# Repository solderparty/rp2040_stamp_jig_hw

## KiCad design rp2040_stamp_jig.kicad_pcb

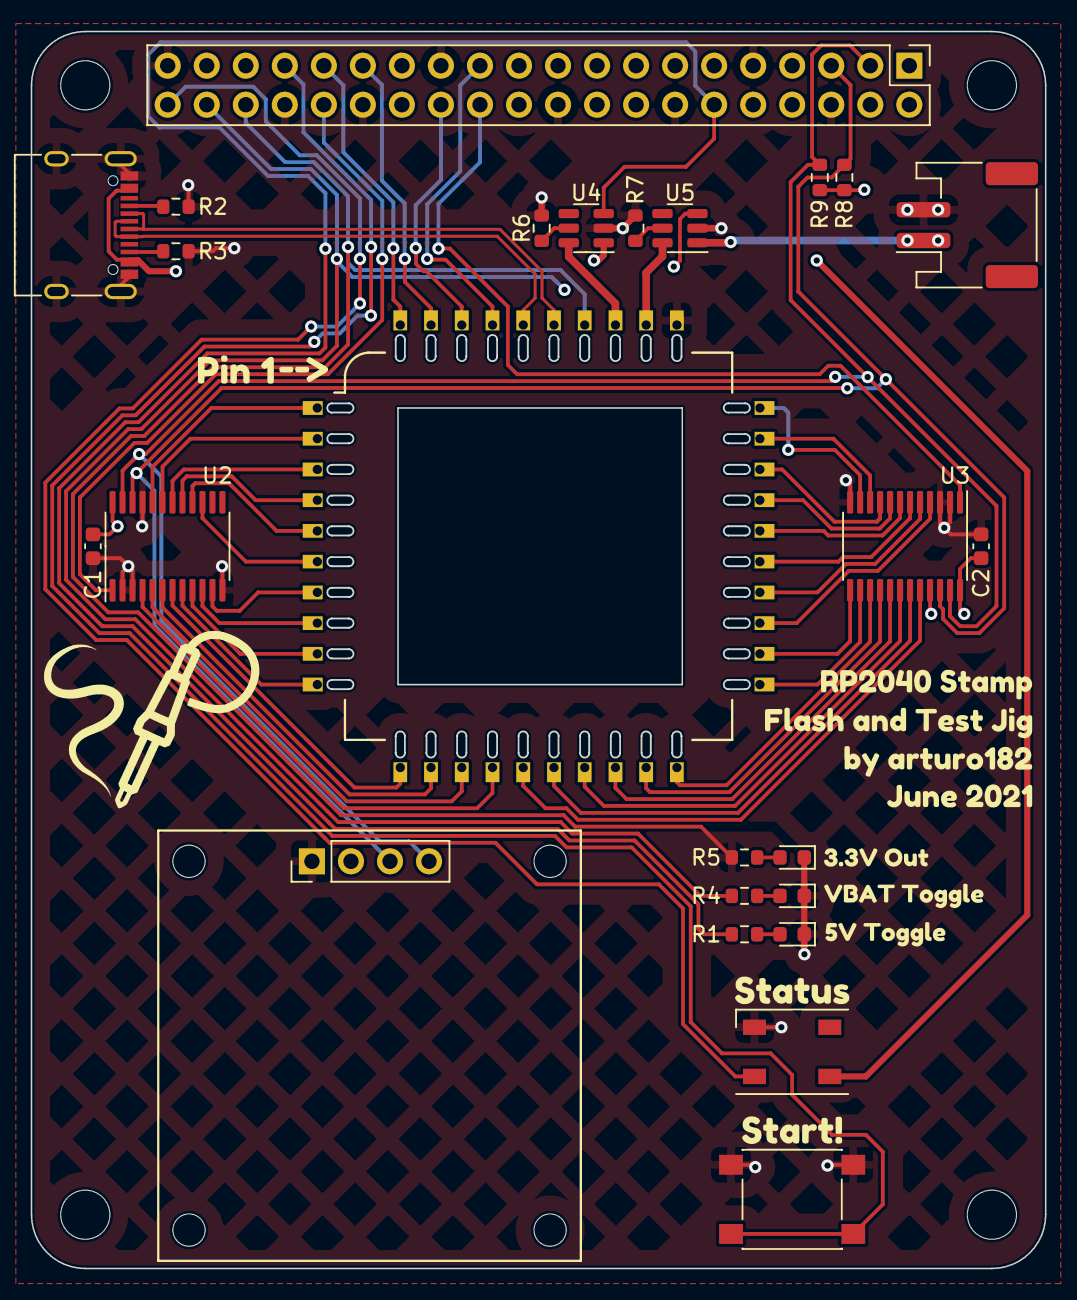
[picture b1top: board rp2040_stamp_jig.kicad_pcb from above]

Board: 4 copper layers, 66.0 x 80.5 mm, 81 parts (0 on the bottom side), 58 nets.

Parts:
C1, C2: 0.1uF; C_0603_1608Metric
D1: LED_5V_TGL; LED_0603_1608Metric
D2, D3: LED_VBAT_TGL; LED_0603_1608Metric
D4: WS2812B; LED_WS2812B_PLCC4_5.0x5.0mm_P3.2mm
H1, H2, H3, H4: MountingHole; MountingHole_3.2mm_M3
J1, J2, J3, J4, J5, J6, J7, J8, J9, J10, J11, J12, J13, J14, J15, J16, J17, J18, J19, J20, J21, J22, J23, J24, J25, J26, J27, J28, J29, J30, J31, J32, J33, J34, J35, J36, J37, J38, J39, J40: Conn_01x01; StampSpring_1x01_P1.00mm_Vertical
J41: USB_C_Receptacle_USB2.0; USB_C_Receptacle_XKB_U262-16XN-4BVC11
J42: Raspberry_Pi_2_3; PinHeader_2x20_P2.54mm_Vertical
J43: Conn_Batt; JST_PH_S2B-PH-SM4-TB_1x02-1MP_P2.00mm_Horizontal
J44: Conn_OLED; PinHeader_1x04_P2.54mm_Vertical
R1, R4, R5: 1K; R_0603_1608Metric
R2, R3: 5.1K; R_0603_1608Metric
R6, R7: 2K; R_0603_1608Metric
R8, R9: 4.7K; R_0603_1608Metric
SW1: BTN_START; SW_SPST_PTS645
U1: RP2040_Stamp; RP2040_Stamp_SMD
U2, U3: PCA9555PW; TSSOP-24_4.4x7.8mm_P0.65mm
U4, U5: TPS255xDBV; SOT-23-6
svg2mod, svg2mod#2, svg2mod#3, svg2mod#4, svg2mod#5, svg2mod#6, svg2mod#7, svg2mod#8, svg2mod#9, svg2mod#10, svg2mod#11, svg2mod#12: G***; svg2mod

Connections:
+3V3: C1.1, C2.1, J42.1 (3V3), J42.17 (3V3), J44.2, R8.1, R9.1, U2.24 (VDD), U3.21 (A0), U3.24 (VDD)
+5V: D4.1 (VDD), J41.A4 (VBUS), J41.A9 (VBUS), J41.B4 (VBUS), J41.B9 (VBUS), U4.1 (IN)
+BATT: J43.1, U5.1 (IN)
/3.3V_OUT: J3.1, J42.36 (GPIO16), R5.2
/5V_IN: J1.1, U4.6 (OUT)
/5V_TOGGLE: J42.12 (GPIO18/PWM0), R1.2, U4.3 (EN)
/BOOTSEL: J8.1, J42.31 (GCLK2/GPIO6)
/BUTTON: J42.33 (PWM1/GPIO13), SW1.1 (A)
/GPIO0: J2.1, U2.20 (IO1_7)
/GPIO1: J4.1, U2.19 (IO1_6)
/GPIO2: J6.1, U2.18 (IO1_5)
/GPIO3: J7.1, U2.17 (IO1_4)
/GPIO4: J9.1, U2.16 (IO1_3)
/GPIO5: J10.1, U2.15 (IO1_2)
/GPIO6: J12.1, U2.11 (IO0_7)
/GPIO7: J13.1, U2.10 (IO0_6)
/GPIO8: J15.1, U2.9 (IO0_5)
/GPIO9: J17.1, U2.8 (IO0_4)
/GPIO10: J18.1, U2.7 (IO0_3)
/GPIO11: J20.1, U2.6 (IO0_2)
/GPIO12: J22.1, U2.5 (IO0_1)
/GPIO13: J23.1, U2.4 (IO0_0)
/GPIO14: J24.1, U3.20 (IO1_7)
/GPIO15: J25.1, U3.19 (IO1_6)
/GPIO16: J26.1, U3.18 (IO1_5)
/GPIO17: J27.1, U3.17 (IO1_4)
/GPIO18: J28.1, U3.16 (IO1_3)
/GPIO19: J29.1, U3.15 (IO1_2)
/GPIO20: J30.1, U3.14 (IO1_1)
/GPIO21: J31.1, U3.13 (IO1_0)
/GPIO22: J32.1, U3.4 (IO0_0)
/GPIO23: J33.1, U3.5 (IO0_1)
/GPIO24: J34.1, U3.6 (IO0_2)
/GPIO25: J35.1, U3.7 (IO0_3)
/GPIO26: J36.1, U3.8 (IO0_4)
/GPIO27: J37.1, U3.9 (IO0_5)
/GPIO28: J38.1, U3.10 (IO0_6)
/GPIO29: J40.1, U3.11 (IO0_7)
/INT_A: J42.32 (PWM0/GPIO12), U2.1 (~INT)
/INT_B: J42.24 (~CE0~/GPIO8), U3.1 (~INT)
/NEOPIXEL: D4.4 (DIN), J42.40 (GPIO21/SCLK1)
/SCL: J42.5 (SCL/GPIO3), J44.3, R8.2, U2.22 (SCL), U3.22 (SCL)
/SDA: J42.3 (SDA/GPIO2), J44.4, R9.2, U2.23 (SDA), U3.23 (SDA)
/SWCLK: J21.1, J42.26 (~CE1~/GPIO7)
/SWDIO: J19.1, J42.23 (SCLK0/GPIO11)
/USB_D+: J16.1, J41.A6 (D+), J41.B6 (D+)
/USB_D-: J14.1, J41.A7 (D-), J41.B7 (D-)
/VBAT: J5.1, U5.6 (OUT)
/VBAT_TOGGLE: J42.38 (GPIO20/MOSI1), R4.2, U5.3 (EN)
/~RESET~: J11.1, J42.29 (GCLK1/GPIO5)
GND: C1.2, C2.2, D1.1 (K), D2.1 (K), D3.1 (K), D4.3 (VSS), J39.1, J41.A1 (GND), J41.A12 (GND), J41.B1 (GND), J41.B12 (GND), J41.S1 (SHIELD), J42.6 (GND), J42.9 (GND), J42.14 (GND), J42.20 (GND), J42.25 (GND), J42.30 (GND), J42.34 (GND), J42.39 (GND), J43.2, J44.1, R2.2, R3.2, R6.1, R7.1, SW1.2 (B), U2.2 (A1), U2.3 (A2), U2.12 (VSS), U2.21 (A0), U3.2 (A1), U3.3 (A2), U3.12 (VSS), U4.2 (GND), U5.2 (GND)
unnamed: D1.2 (A), R1.1
unnamed: D2.2 (A), R4.1
unnamed: D3.2 (A), R5.1
unnamed: J41.A5 (CC1), R2.1
unnamed: J41.B5 (CC2), R3.1
unnamed: R6.2, U4.5 (ILIM)
unnamed: R7.2, U5.5 (ILIM)

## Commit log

2022-02-21 Initial import
